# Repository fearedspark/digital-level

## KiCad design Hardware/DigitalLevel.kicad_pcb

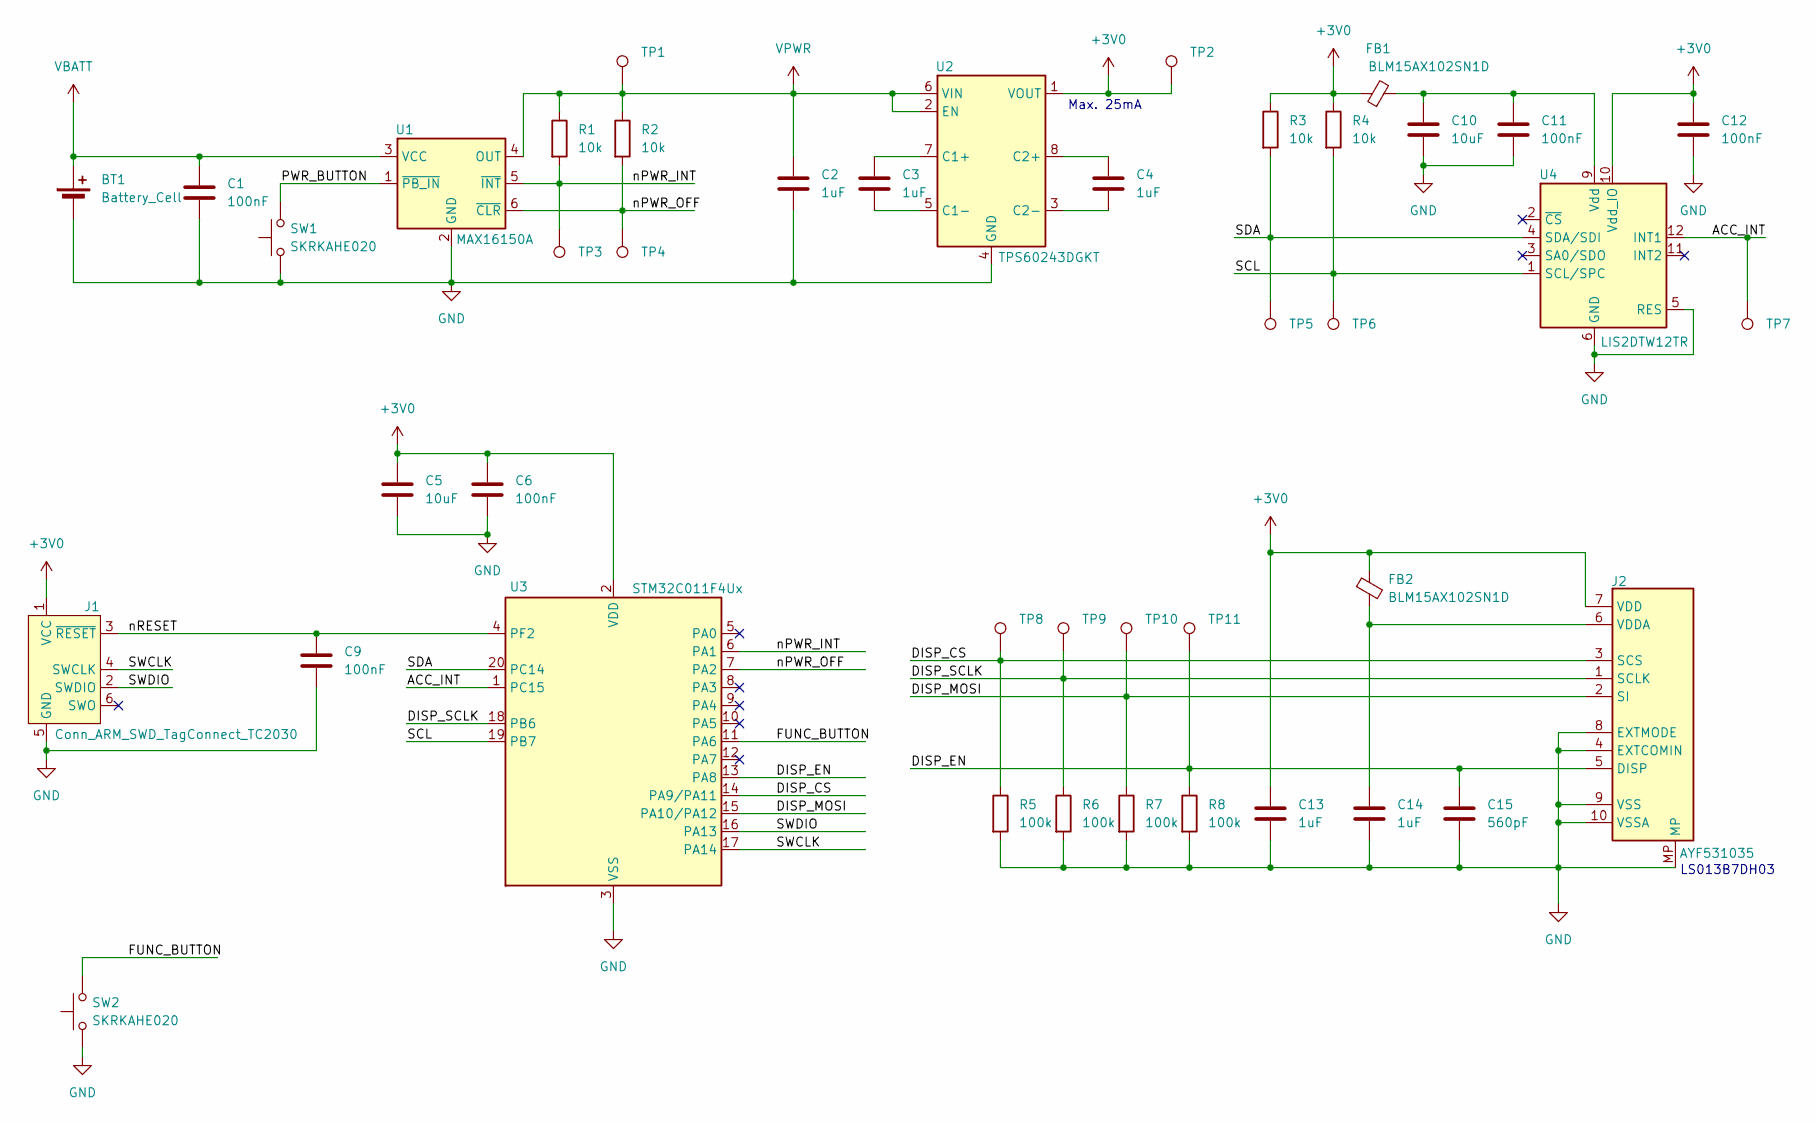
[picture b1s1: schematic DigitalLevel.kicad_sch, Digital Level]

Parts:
BT1: Battery_Cell; BatteryHolder_Keystone_1058_1x2032
C1, C6, C9, C11, C12: 100nF; C_0402_1005Metric
C2, C3, C4, C13, C14: 1uF; C_0402_1005Metric
C5, C10: 10uF; C_0402_1005Metric
C15: 560pF; C_0402_1005Metric
FB1, FB2: BLM15AX102SN1D; L_0402_1005Metric
J1: Conn_ARM_SWD_TagConnect_TC2030; Tag-Connect_TC2030-IDC-FP_2x03_P1.27mm_Vertical
J2: AYF531035; LS013B7DH03
R1, R2: 10k; R_0402_1005Metric
R3, R4: 10k; R_0603_1608Metric
R5, R6, R7, R8: 100k; R_0603_1608Metric
SW1, SW2: SKRKAHE020; SW_Push_SPST_NO_Alps_SKRK
TP1, TP2, TP3, TP4, TP5, TP6, TP7, TP8, TP9, TP10, TP11: TestPoint; TestPoint_Pad_D1.0mm
U1: MAX16150A; TSOT-23-6_HandSoldering
U2: TPS60243DGKT; VSSOP-8_3x3mm_P0.65mm
U3: STM32C011F4Ux; ST_UFQFPN-20_3x3mm_P0.5mm
U4: LIS2DTW12TR; LGA-12_2x2mm_P0.5mm

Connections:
+3V0: C5.1, C6.1, C12.1, C13.1, FB1.1, FB2.1, J1.1 (VCC), J2.7 (VDD), R3.1, R4.1, TP2.1, U2.1 (VOUT), U3.2 (VDD), U4.10 (Vdd_IO)
/ACC_INT: TP7.1, U3.1 (PC15), U4.12 (INT1)
/DISP_CS: J2.3 (SCS), R5.1, TP8.1, U3.14 (PA9/PA11)
/DISP_EN: C15.1, J2.5 (DISP), R8.1, TP11.1, U3.13 (PA8)
/DISP_MOSI: J2.2 (SI), R7.1, TP10.1, U3.15 (PA10/PA12)
/DISP_SCLK: J2.1 (SCLK), R6.1, TP9.1, U3.18 (PB6)
/FUNC_BUTTON: SW2.2, U3.11 (PA6)
/PWR_BUTTON: SW1.2, U1.1 (~PB_IN)
/SCL: R4.2, TP6.1, U3.19 (PB7), U4.1 (SCL/SPC)
/SDA: R3.2, TP5.1, U3.20 (PC14), U4.4 (SDA/SDI)
/SWCLK: J1.4 (SWCLK), U3.17 (PA14)
/SWDIO: J1.2 (SWDIO), U3.16 (PA13)
/nPWR_INT: R1.2, TP3.1, U1.5 (~INT), U3.6 (PA1)
/nPWR_OFF: R2.2, TP4.1, U1.6 (~CLR), U3.7 (PA2)
/nRESET: C9.1, J1.3 (~RESET), U3.4 (PF2)
GND: BT1.2 (-), C1.2, C2.2, C5.2, C6.2, C9.2, C10.2, C11.2, C12.2, C13.2, C14.2, C15.2, J1.5 (GND), J2.4 (EXTCOMIN), J2.8 (EXTMODE), J2.9 (VSS), J2.10 (VSSA), J2.MP, R5.2, R6.2, R7.2, R8.2, SW1.1, SW2.1, U1.2 (GND), U2.4 (GND), U3.3 (VSS), U4.5 (RES), U4.6 (GND), U4.7 (GND), U4.8 (GND)
unnamed: C14.1, FB2.2, J2.6 (VDDA)
unnamed: C3.1, U2.7 (C1+)
unnamed: C3.2, U2.5 (C1-)
unnamed: C4.1, U2.8 (C2+)
unnamed: C4.2, U2.3 (C2-)
unnamed: C10.1, C11.1, FB1.2, U4.9 (Vdd)
VBATT: BT1.1 (+), C1.1, U1.3 (VCC)
VPWR: C2.1, R1.1, R2.1, TP1.1, U1.4 (OUT), U2.2 (EN), U2.6 (VIN)

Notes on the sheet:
LS013B7DH03
Max. 25mA

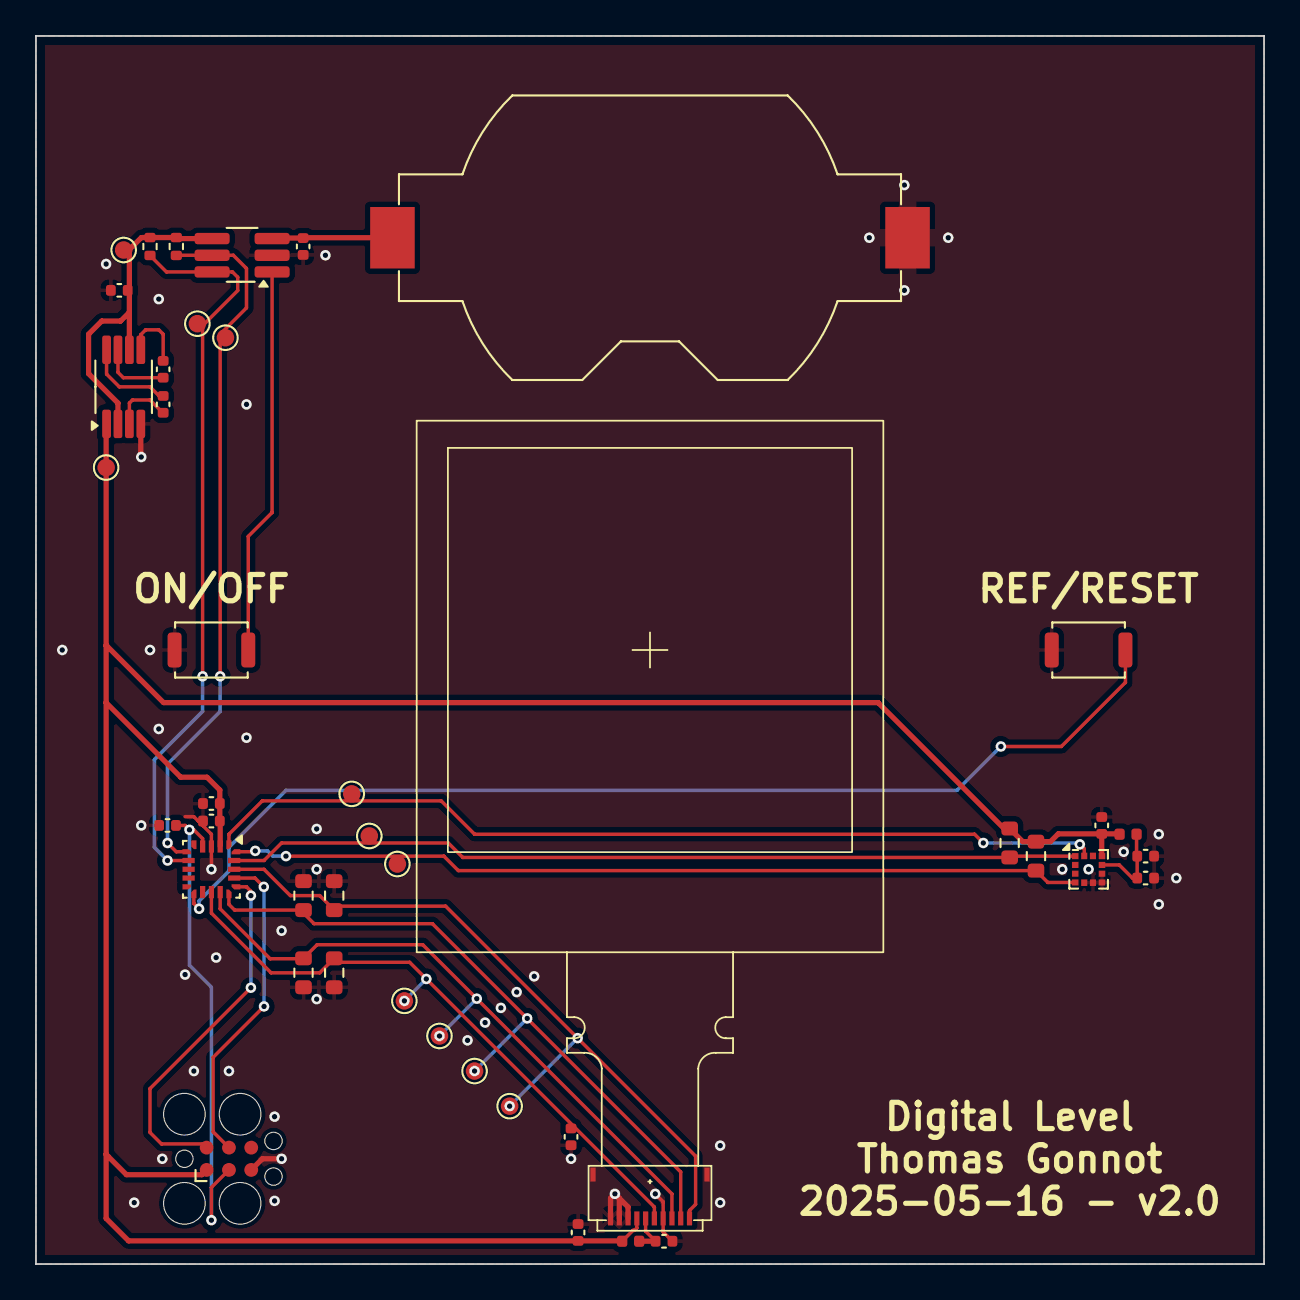
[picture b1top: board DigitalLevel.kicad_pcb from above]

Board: 2 copper layers, 70.0 x 70.0 mm, 43 parts (0 on the bottom side), 24 nets.

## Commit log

2024-11-14 Added initial board design
2024-11-14 Configured Gerber output folder
2025-05-16 Upgraded project for KiCad v9
2025-05-16 Swap MCU to STM32C0
